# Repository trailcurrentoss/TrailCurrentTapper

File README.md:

# TrailCurrent Tapper

Eight-button control panel that sends device commands and brightness control over a CAN bus interface with OTA firmware update capability. Part of the [TrailCurrent](https://trailcurrent.com) open-source vehicle platform.

## Hardware Overview

- **Microcontroller:** ESP32 (WROOM32)
- **Function:** Physical button panel for CAN bus device control
- **Key Features:**
  - 8 momentary buttons with LED backlights
  - Short press: toggle device on/off
  - Long press (hold 700ms+): brightness adjustment (0-255)
  - CAN bus communication at 500 kbps
  - Over-the-air (OTA) firmware updates via WiFi
  - LED state feedback from CAN bus
  - FreeCAD enclosure design

## Hardware Requirements

### Components

- **Microcontroller:** ESP32 development board
- **CAN Transceiver:** Vehicle CAN bus interface (TX: GPIO 15, RX: GPIO 13)

### Pin Connections

**Buttons (INPUT_PULLUP):**

| GPIO | Function |
|------|----------|
| 34 | Button 1 |
| 25 | Button 2 |
| 27 | Button 3 |
| 12 | Button 4 |
| 16 | Button 5 |
| 22 | Button 6 |
| 21 | Button 7 |
| 18 | Button 8 |

**LED Backlights (OUTPUT):**

| GPIO | Function |
|------|----------|
| 32 | LED 1 |
| 33 | LED 2 |
| 26 | LED 3 |
| 14 | LED 4 |
| 4 | LED 5 |
| 23 | LED 6 |
| 19 | LED 7 |
| 17 | LED 8 |

### KiCAD Library Dependencies

This project uses the consolidated [TrailCurrentKiCADLibraries](https://github.com/trailcurrentoss/TrailCurrentKiCADLibraries).

**Setup:**

```bash
# Clone the library
git clone git@github.com:trailcurrentoss/TrailCurrentKiCADLibraries.git

# Set environment variables (add to ~/.bashrc or ~/.zshrc)
export TRAILCURRENT_SYMBOL_DIR="/path/to/TrailCurrentKiCADLibraries/symbols"
export TRAILCURRENT_FOOTPRINT_DIR="/path/to/TrailCurrentKiCADLibraries/footprints"
export TRAILCURRENT_3DMODEL_DIR="/path/to/TrailCurrentKiCADLibraries/3d_models"
```

See [KICAD_ENVIRONMENT_SETUP.md](https://github.com/trailcurrentoss/TrailCurrentKiCADLibraries/blob/main/KICAD_ENVIRONMENT_SETUP.md) in the library repository for detailed setup instructions.

## Opening the Project

1. **Set up environment variables** (see Library Dependencies above)
2. **Open KiCAD:**
   ```bash
   kicad EDA/trailcurrent-tapper.kicad_pro
   ```
3. **Verify libraries load** - All symbol and footprint libraries should resolve without errors
4. **View 3D models** - Open PCB and press `Alt+3` to view the 3D visualization

## Firmware

See `src/` directory for PlatformIO-based firmware.

**Setup:**
```bash
# Install PlatformIO (if not already installed)
pip install platformio

# Build firmware
pio run

# Upload to board (serial)
pio run -t upload

# Upload via OTA (after initial flash)
pio run -t upload --upload-port esp32-DEVICE_ID
```

### Firmware Dependencies

This firmware depends on the following public libraries:

- **[OtaUpdateLibraryWROOM32](https://github.com/trailcurrentoss/OtaUpdateLibraryWROOM32)** (v0.0.1) - Over-the-air firmware update functionality
- **[TwaiTaskBasedLibraryWROOM32](https://github.com/trailcurrentoss/TwaiTaskBasedLibraryWROOM32)** (v0.0.1) - CAN bus communication interface

All dependencies are automatically resolved by PlatformIO during the build process.

### CAN Bus Protocol

**Transmit (Panel to Bus):**

| CAN ID | Bytes | Description |
|--------|-------|-------------|
| 0x18 | 1 | Button toggle (byte 0 = button index 0-7) |
| 0x15 | 2 | Brightness control (byte 0 = device index, byte 1 = brightness 0-255) |

**Receive (Bus to Panel):**

| CAN ID | Bytes | Description |
|--------|-------|-------------|
| 0x00 | 3 | OTA update trigger (MAC-based device targeting) |
| 0x1B | 8 | LED backlight state (1 byte per LED, 0=off, non-zero=on) |

### Button Behavior

- **Short press** (< 700ms): Sends toggle command on CAN ID 0x18
- **Long hold** (>= 700ms): Enters brightness mode, incrementing brightness every 100ms and sending on CAN ID 0x15
- **Release after hold**: Locks brightness at current value

## Manufacturing

- **PCB Files:** Ready for fabrication via standard PCB services (JLCPCB, OSH Park, etc.)
- **BOM Generation:** Export BOM from KiCAD schematic (Tools > Generate BOM)
- **Enclosure:** FreeCAD design included in `CAD/` directory
- **JLCPCB Assembly:** See [BOM_ASSEMBLY_WORKFLOW.md](https://github.com/trailcurrentoss/TrailCurrentKiCADLibraries/blob/main/BOM_ASSEMBLY_WORKFLOW.md) for detailed assembly workflow

## Project Structure

```
├── CAD/                          # FreeCAD enclosure design
├── EDA/                          # KiCAD hardware design files
│   ├── trailcurrent-tapper.kicad_pro
│   ├── trailcurrent-tapper.kicad_sch
│   └── trailcurrent-tapper.kicad_pcb
├── src/                          # Firmware source
│   ├── main.cpp                  # Button handling and CAN communication
│   ├── globals.h                 # LED pin definitions
│   ├── debug.h                   # Comprehensive debug macro system
│   ├── canHelper.h               # CAN bus configuration
│   └── Secrets.h.template        # WiFi credentials template
├── ARCHITECTURE_CORRECTED.md     # Architecture documentation
├── BUTTON_LED_FIX_SUMMARY.md     # Button/LED fix notes
├── platformio.ini                # Build configuration
└── partitions.csv                # ESP32 flash partition layout
```

## License

MIT License - See LICENSE file for details.

## Contributing

Improvements and contributions are welcome! Please submit issues or pull requests.

## Support

For questions about:
- **KiCAD setup:** See [KICAD_ENVIRONMENT_SETUP.md](https://github.com/trailcurrentoss/TrailCurrentKiCADLibraries/blob/main/KICAD_ENVIRONMENT_SETUP.md)
- **Assembly workflow:** See [BOM_ASSEMBLY_WORKFLOW.md](https://github.com/trailcurrentoss/TrailCurrentKiCADLibraries/blob/main/BOM_ASSEMBLY_WORKFLOW.md)

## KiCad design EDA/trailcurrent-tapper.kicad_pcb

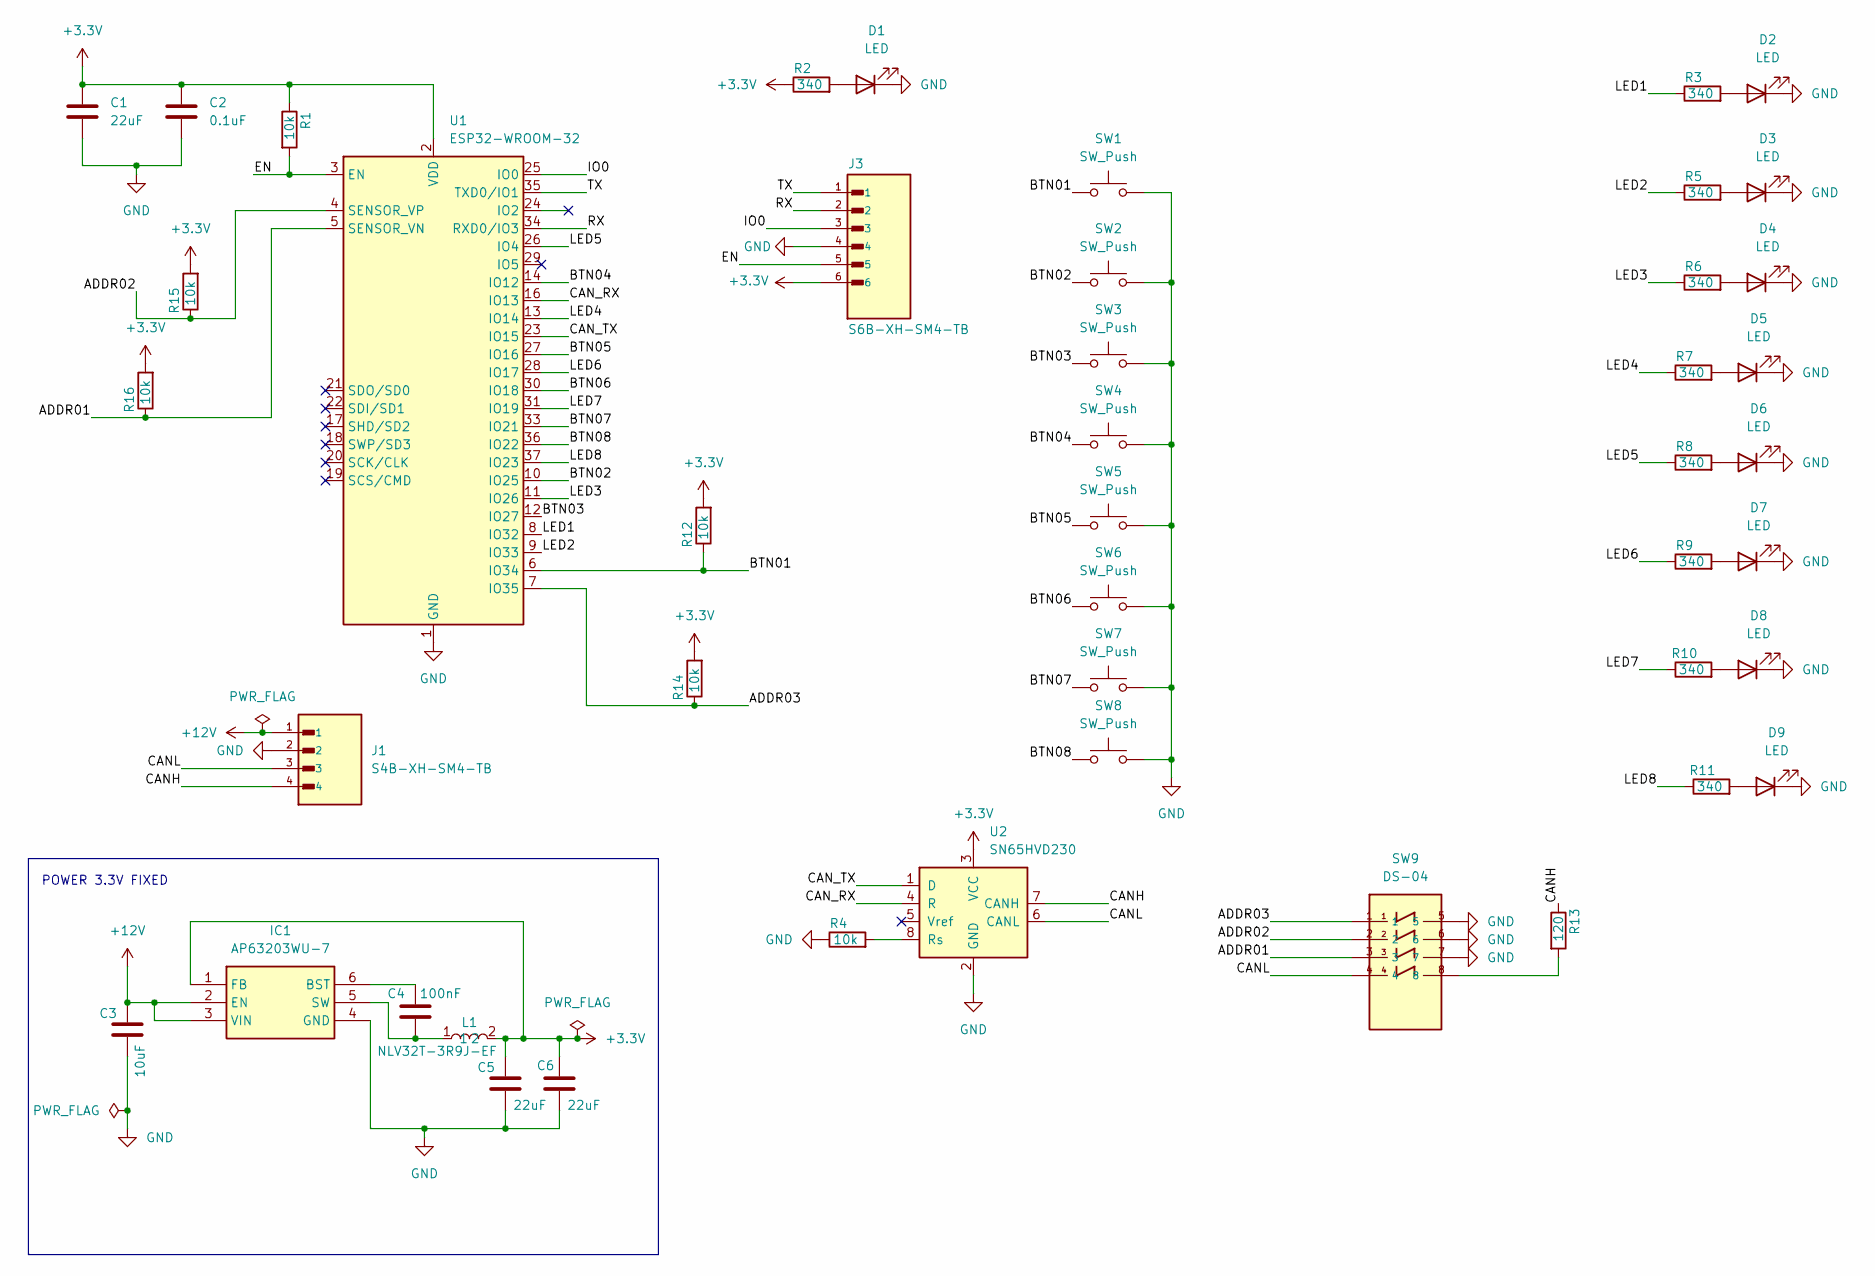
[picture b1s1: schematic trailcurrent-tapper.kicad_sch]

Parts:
C1, C5, C6: 22uF; C_1206_3216Metric_Pad1.33x1.80mm_HandSolder
C2: 0.1uF; C_1206_3216Metric_Pad1.33x1.80mm_HandSolder
C3: 10uF; C_1206_3216Metric
C4: 100nF; C_1206_3216Metric
D1, D2, D3, D4, D5, D6, D7, D8, D9: LED; LED_1206_3216Metric_Pad1.42x1.75mm_HandSolder
IC1: AP63203WU-7; AP63203WU7; Mouser Part Number 621-AP63203WU-7
J1: S4B-XH-SM4-TB; JST_S4B-XH-SM4-TB; LCSC Part C161861
J3: S6B-XH-SM4-TB; JST_S6B-XH-SM4-TB; LCSC Part C191914
L1: NLV32T-3R9J-EF; Manufacturer_Part_Number NLV32T-3R9J-EF; Mouser Part Number 810-NLV32T3R9JEF
R1, R4, R12, R14, R15, R16: 10k; R_1206_3216Metric_Pad1.30x1.75mm_HandSolder
R2, R3, R5, R6, R7, R8, R9, R10, R11: 340; R_1206_3216Metric_Pad1.30x1.75mm_HandSolder
R13: 120; R_1206_3216Metric_Pad1.30x1.75mm_HandSolder
SW1, SW2, SW3, SW4, SW5, SW6, SW7, SW8: SW_Push; SW_PUSH_6mm
SW9: DS-04; Manufacturer_Part_Number DS-04
U1: ESP32-WROOM-32; ESP32-WROOM-32U
U2: SN65HVD230; SOIC-8_3.9x4.9mm_P1.27mm

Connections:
+3.3V: C1.1, C2.1, C5.1, C6.1, IC1.1 (FB), J3.6, L1.2, R1.1, R2.1, R12.2, R14.2, R15.2, R16.2, U1.2 (VDD), U2.3 (VCC)
+12V: C3.1, IC1.2 (EN), IC1.3 (VIN), J1.1
/ADDR01: R16.1, SW9.3, U1.5 (SENSOR_VN)
/ADDR02: R15.1, SW9.2, U1.4 (SENSOR_VP)
/ADDR03: R14.1, SW9.1, U1.7 (IO35)
/BTN01: R12.1, SW1.1, U1.6 (IO34)
/BTN02: SW2.1, U1.10 (IO25)
/BTN03: SW3.1, U1.12 (IO27)
/BTN04: SW4.1, U1.14 (IO12)
/BTN05: SW5.1, U1.27 (IO16)
/BTN06: SW6.1, U1.30 (IO18)
/BTN07: SW7.1, U1.33 (IO21)
/BTN08: SW8.1, U1.36 (IO22)
/CANH: J1.4, R13.1, U2.7 (CANH)
/CANL: J1.3, SW9.4, U2.6 (CANL)
/CAN_RX: U1.16 (IO13), U2.4 (R)
/CAN_TX: U1.23 (IO15), U2.1 (D)
/EN: J3.5, R1.2, U1.3 (EN)
/IO0: J3.3, U1.25 (IO0)
/LED1: R3.1, U1.8 (IO32)
/LED2: R5.1, U1.9 (IO33)
/LED3: R6.1, U1.11 (IO26)
/LED4: R7.1, U1.13 (IO14)
/LED5: R8.1, U1.26 (IO4)
/LED6: R9.1, U1.28 (IO17)
/LED7: R10.1, U1.31 (IO19)
/LED8: R11.1, U1.37 (IO23)
/RX: J3.2, U1.34 (RXD0/IO3)
/TX: J3.1, U1.35 (TXD0/IO1)
GND: C1.2, C2.2, C3.2, C5.2, C6.2, D1.1 (K), D2.1 (K), D3.1 (K), D4.1 (K), D5.1 (K), D6.1 (K), D7.1 (K), D8.1 (K), D9.1 (K), IC1.4 (GND), J1.2, J3.4, R4.1, SW1.2, SW2.2, SW3.2, SW4.2, SW5.2, SW6.2, SW7.2, SW8.2, SW9.5, SW9.6, SW9.7, U1.1 (GND), U1.15 (GND), U1.38 (GND), U1.39 (GND), U2.2 (GND)
unnamed: D1.2 (A), R2.2
unnamed: D2.2 (A), R3.2
unnamed: D3.2 (A), R5.2
unnamed: D4.2 (A), R6.2
unnamed: D5.2 (A), R7.2
unnamed: D6.2 (A), R8.2
unnamed: D7.2 (A), R9.2
unnamed: D8.2 (A), R10.2
unnamed: D9.2 (A), R11.2
unnamed: C4.1, IC1.6 (BST)
unnamed: C4.2, IC1.5 (SW), L1.1
unnamed: R13.2, SW9.8
unnamed: R4.2, U2.8 (Rs)

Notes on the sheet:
POWER 3.3V FIXED

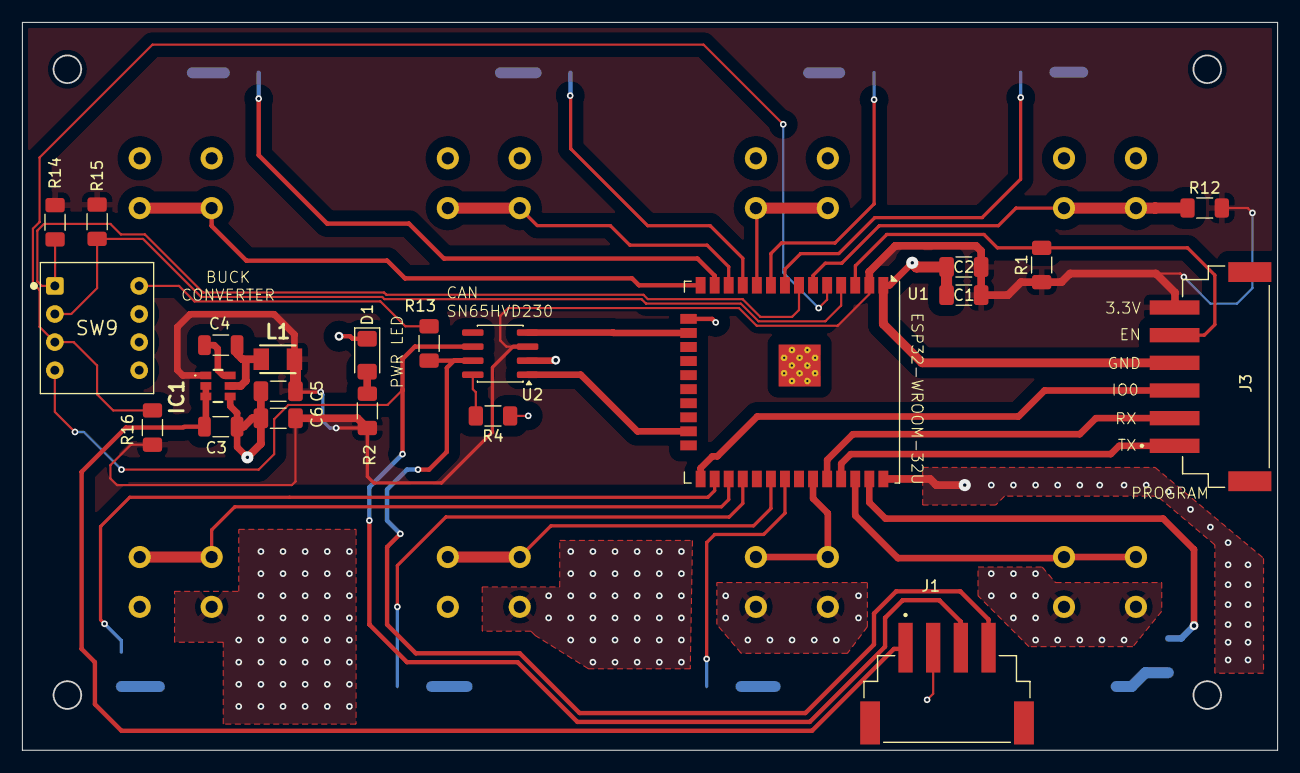
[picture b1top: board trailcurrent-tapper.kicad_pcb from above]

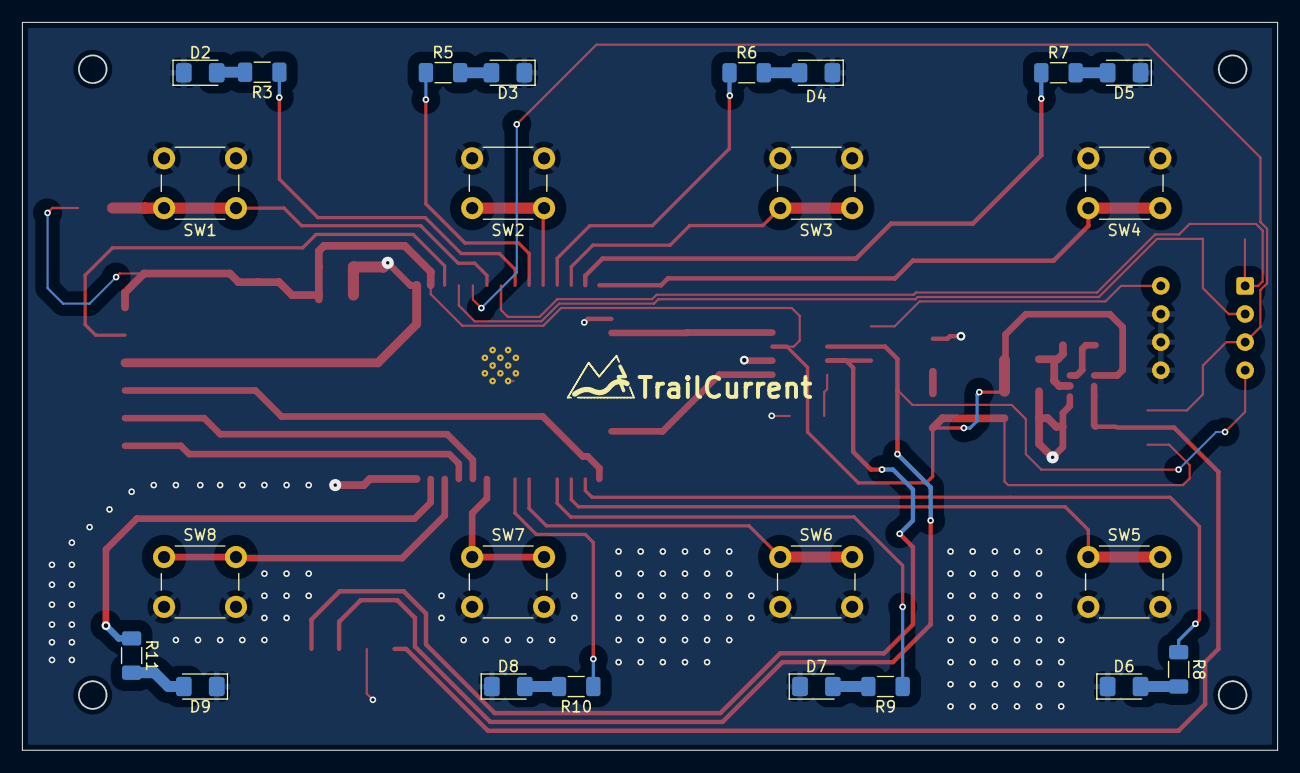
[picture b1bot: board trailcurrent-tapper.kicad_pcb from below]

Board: 2 copper layers, 113.3 x 65.7 mm, 48 parts (25 on the bottom side), 43 nets.

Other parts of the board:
LOGO: TrailCurrentLogo_Text
LOGO#2: TrailCurrentLogo_Icon

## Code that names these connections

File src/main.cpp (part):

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      debugln("[LED] LED state update received");

      // Update LED backlights based on received state
      digitalWrite(LED1_PIN, msg.data[0] > 0 ? HIGH : LOW);
      digitalWrite(LED2_PIN, msg.data[1] > 0 ? HIGH : LOW);
      digitalWrite(LED3_PIN, msg.data[2] > 0 ? HIGH : LOW);
      digitalWrite(LED4_PIN, msg.data[3] > 0 ? HIGH : LOW);
      digitalWrite(LED5_PIN, msg.data[4] > 0 ? HIGH : LOW);
      digitalWrite(LED6_PIN, msg.data[5] > 0 ? HIGH : LOW);
      digitalWrite(LED7_PIN, msg.data[6] > 0 ? HIGH : LOW);
      digitalWrite(LED8_PIN, msg.data[7] > 0 ? HIGH : LOW);

      debugf("[LED] Backlight states: %d,%d,%d,%d,%d,%d,%d,%d\n",
             msg.data[0], msg.data[1], msg.data[2], msg.data[3],
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  debugln("CAN Bus Control with OTA Updates");

  // Initialize LED pins (outputs)
  pinMode(LED1_PIN, OUTPUT);
  pinMode(LED2_PIN, OUTPUT);
  pinMode(LED3_PIN, OUTPUT);
  pinMode(LED4_PIN, OUTPUT);
  pinMode(LED5_PIN, OUTPUT);
  pinMode(LED6_PIN, OUTPUT);
  pinMode(LED7_PIN, OUTPUT);
  pinMode(LED8_PIN, OUTPUT);

  // Turn off all LEDs initially
  digitalWrite(LED1_PIN, LOW);
  digitalWrite(LED2_PIN, LOW);
  digitalWrite(LED3_PIN, LOW);
  digitalWrite(LED4_PIN, LOW);
  digitalWrite(LED5_PIN, LOW);
  digitalWrite(LED6_PIN, LOW);
  digitalWrite(LED7_PIN, LOW);
  digitalWrite(LED8_PIN, LOW);

  debugln("[LED] All LEDs initialized to OFF");

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
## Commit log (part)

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2026-02-23 Add trailcurrent.com link to README
2026-02-28 Updated PCB to use JST XH connectors
2026-02-28 Added DIP switch for CAN Termination and device ID settings
2026-03-08 Aligning with new product names
2026-03-08 Aligning with product names
